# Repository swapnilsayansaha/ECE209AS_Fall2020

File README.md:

# GUI-GAN and HMM-T9
Course project repository (Bake-Off 1 and Bake-off 2) for ECE 209AS Fall 2020 (Human Computer Interaction). (c) 2020 Viacheslav Inderiakin and Swapnil Sayan Saha.

# Project 1

HMM-T9 is a tiny T9 keyboard using Hidden Markov Models (HMM) for GUI-based text prediction, with a contact area of ~2.95 cm<sup>2</sup> while achieving ~9 WPM.

# Project 2

*Elevator Pitch: We have designed a graphical framework for generating large amounts of realistic but privacy-preserving synthetic sensory data from limited real-world data in any discipline, while also allowing the user to modify the generated data using graphical tools.*

Demo Video: https://youtu.be/b78lVvjH8vc 

GUI-GAN is a real-time and interactive graphical user interface (GUI) framework for synthesizing large time-series datasets from moderately-sized input datasets using Generative Adversarial Networks (GANs). Specifically, we illustrate a generalizable graphical pipeline powered by a deep-learning backend that allows non-experts to generate synthetic sensory data while parameterizing synthetic data statistics via graphical tools. In addition, the framework allows the user specify rectification statistics of generated data via graphs and symbols, which is then fed to another generative deep-learning pipeline for data imputation based on user-corrections. Features of the framework are:

* Generates privacy preserving annotated multi-class datasets from small time-series datasets in any domain
* Collaborative and controllable: allows user to make graph-based and symbolic corrections to groups of generated datasets as well as control GAN parameters in non-technical manner.
* Aimed for non-experts: assumes zero machine-learning and coding expertise; runs on any generic computing device without requiring expensive computing equipment

For data synthesis, we input the data and user conditions to a VAE generator based GAN called PhysioGAN (https://escholarship.org/uc/item/3xm7j6nw). The encoder-decoder networks map training data to latent space and perform reconstruction, while the discriminator forces the generator to follow the coveted data distribution as closely as possible. (For mid-term prototype, we used a simplified version of PhysioGAN called SenseGen (https://ieeexplore.ieee.org/document/7917555)). For data imputation, we feed the input data, mask metadata characterizing missing data and a random matrix to the generator network, while the discriminator uses the generator output (imputed data) coupled with a hint matrix to try and distinguish between observed and imputed components. This model is called GAIN (http://proceedings.mlr.press/v80/yoon18a/yoon18a.pdf).

References:
1. Alzantot, Moustafa Farid Taha Mohammed. “Secure and Private Machine Learning for Smart Devices”. Ph.D. Diss. UCLA, 2019.
2. Yoon, Jinsung, James Jordon, and Mihaela van der Schaar. " GAIN: Missing Data Imputation using Generative Adversarial Nets. " International Conference on Machine Learning (ICML). 2018.
3. Alzantot, Moustafa, Supriyo Chakraborty, and Mani Srivastava. "Sensegen: A deep learning architecture for synthetic sensor data generation." 2017 IEEE International Conference on Pervasive Computing and Communications Workshops (PerCom Workshops). IEEE, 2017.

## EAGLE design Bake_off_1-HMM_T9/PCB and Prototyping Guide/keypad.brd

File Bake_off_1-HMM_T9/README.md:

# HMM-T9: An AI-enabled Tiny T9 Keyboard

HMM-T9 is a tiny T9 keyboard using Hidden Markov Models (HMM) for GUI-based text prediction, with a contact area of ~2.95 cm<sup>2</sup> while achieving ~9 WPM.

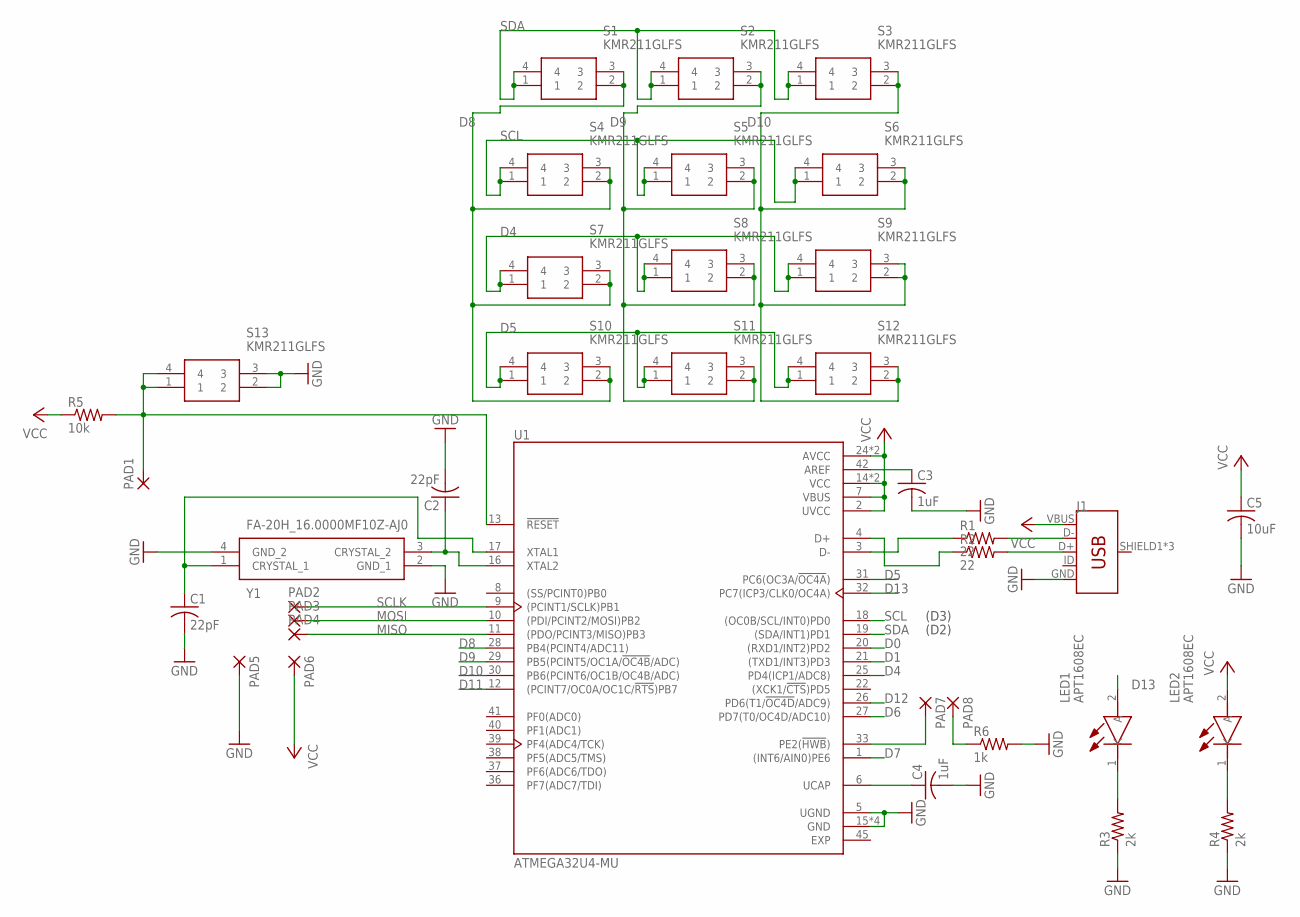
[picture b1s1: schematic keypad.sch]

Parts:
C1, C2: 22pF; C0603
C3, C4: 1uF; C0603
C5: 10uF; C0603
J1: USB_MICRO-BREDUCED_PASTE; USB-B-MICRO-SMD_RED_PASTE
LED1, LED2: APT1608EC; LEDC1608X85N
PAD1, PAD2, PAD3, PAD4, PAD5, PAD6, PAD7, PAD8: SMD2; SMD1,27-2,54
R1, R2: 22; R0603
R3, R4: 2k; R0603
R5: 10k; R0603
R6: 1k; R0603
S1, S2, S3, S4, S5, S6, S7, S8, S9, S10, S11, S12, S13: KMR211GLFS; KMR2_1
U1: ATMEGA32U4-MU; QFN50P700X700X100-45N
Y1: FA-20H_16.0000MF10Z-AJ0; FA20H160000MF12ZAC3

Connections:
D0: U1.20 ((RXD1/INT2)PD2)
D1: U1.21 ((TXD1/INT3)PD3)
D4: S7.1, S7.4, S8.1, S8.4, S9.1, S9.4, U1.25 (PD4(ICP1/ADC8))
D5: S10.1, S10.4, S11.1, S11.4, S12.1, S12.4, U1.31 (PC6(OC3A/!OC4A!))
D6: U1.27 (PD7(T0/OC4D/ADC10))
D7: U1.1 ((INT6/AIN0)PE6)
D8: S1.2, S1.3, S4.2, S4.3, S7.2, S7.3, S10.2, S10.3, U1.28 (PB4(PCINT4/ADC11))
D9: S2.2, S2.3, S5.2, S5.3, S8.2, S8.3, S11.2, S11.3, U1.29 (PB5(PCINT5/OC1A/!OC4B!/ADC))
D10: S3.2, S3.3, S6.2, S6.3, S9.2, S9.3, S12.2, S12.3, U1.30 (PB6(PCINT6/OC1B/OC4B/ADC))
D11: U1.12 ((PCINT7/OC0A/OC1C/!RTS!)PB7)
D12: U1.26 (PD6(T1/!OC4D!/ADC9))
D13: LED1.2 (A), U1.32 (PC7(ICP3/CLK0/OC4A))
GND: C1.2, C2.2, C3.2, C4.2, C5.2, J1.GND, PAD5.1, R3.1, R4.1, R6.2, S13.2, S13.3, U1.5 (UGND), U1.15 (GND), U1.23 (GND), U1.35 (GND), U1.43 (GND), Y1.2 (GND_1), Y1.4 (GND_2)
MISO: PAD4.1, U1.11 ((PDO/PCINT3/MISO)PB3)
MOSI: PAD3.1, U1.10 ((PDI/PCINT2/MOSI)PB2)
unnamed: LED2.1 (K), R4.2
unnamed: PAD8.1, R6.1
unnamed: PAD7.1, U1.33 (PE2(!HWB!))
unnamed: C2.1, U1.16 (XTAL2), Y1.3 (CRYSTAL_2)
unnamed: C1.1, U1.17 (XTAL1), Y1.1 (CRYSTAL_1)
unnamed: C3.1, U1.42 (AREF)
unnamed: C4.1, U1.6 (UCAP)
unnamed: J1.D-, R1.2
unnamed: J1.D+, R2.2
unnamed: R1.1, U1.3 (D-)
unnamed: R2.1, U1.4 (D+)
unnamed: PAD1.1, R5.2, S13.1, S13.4, U1.13 (!RESET!)
unnamed: LED1.1 (K), R3.2
SCL: S4.1, S4.4, S5.1, S5.4, S6.1, S6.4, U1.18 ((OC0B/SCL/INT0)PD0)
SCLK: PAD2.1, U1.9 ((PCINT1/SCLK)PB1)
SDA: S1.1, S1.4, S2.1, S2.4, S3.1, S3.4, U1.19 ((SDA/INT1)PD1)
VCC: C5.1, J1.VBUS, LED2.2 (A), PAD6.1, R5.1, U1.2 (UVCC), U1.7 (VBUS), U1.14 (VCC), U1.24 (AVCC), U1.34 (VCC), U1.44 (AVCC)

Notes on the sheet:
(D2)
(D3)

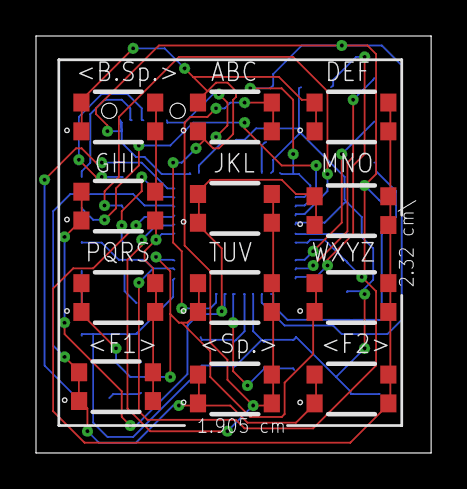
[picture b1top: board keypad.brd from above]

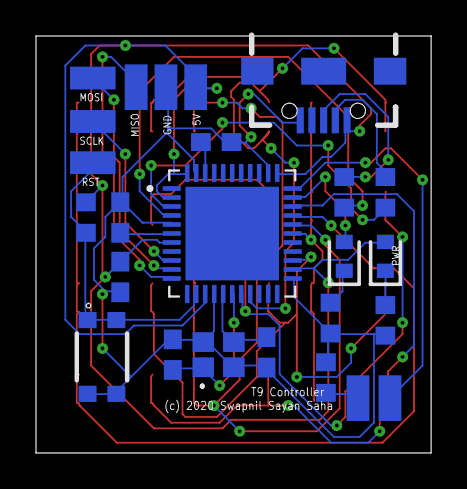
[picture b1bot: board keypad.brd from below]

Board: 2 copper layers, 22.0 x 23.2 mm, 37 parts (25 on the bottom side), 26 nets.

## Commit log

2020-10-25 Baselines
2020-10-25 Smartwatch baseline
2020-10-25 Added survey and interview forms
2020-10-26 Baselines added
2020-10-26 Arduino code for our demo
2020-10-26 HMM NLP
2020-10-26 Python code for our demo
2020-10-26 Training set used for HMM
2020-10-26 Added PCB and Prototyping Guide
2020-10-26 Python demo for our project
2020-10-27 SUS and TLX survey results
2020-10-27 Added SUS, TLX results
2020-10-27 Added SUS, TLX survey results
2020-10-28 Added SUS, TLX results and statistical test file
2020-10-28 Added SUS, TLX scores and statistical test file
2020-10-28 Added presentation and demo
2020-10-28 Added presentation + demo files
2020-11-12 Bake off 1 files
2020-11-12 Bake-off 1 files
2020-11-12 Reorganized bake-off 1 files
2020-11-12 Bake off 2 files
2020-11-12 Added bake-off 2 files
2020-11-12 Added proposal
2020-11-16 Updated Demo
2020-11-16 Updated data loaders
2020-11-16 Updated data synth to work with matrix
2020-11-16 Updated impute file to work with matrix
2020-11-16 Added a zip file
2020-11-23 Remove old dir
2020-11-23 Added bbake off 2 mid term files
2020-11-23 Updated presentation
2020-12-16 Updated requirements.txt
2020-12-16 Added final demo
2020-12-16 Added sample dataset
2020-12-16 Added user study results
2020-12-17 Final presentation added

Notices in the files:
Bake_off_1-HMM_T9/PCB and Prototyping Guide/keypad.brd:
(c) 2020 Swapnil Sayan Saha
parts and their libraries:
SparkFun-Connectors: Licensing: Creative Commons ShareAlike 4.0 International - https://creativecommons.org/licenses/by-sa/4.0
